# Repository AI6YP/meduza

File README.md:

## Meduza

Miniature control/logger board. Part of the Naut /nøyːt/ project.

### PCB v1

[Schematic (PDF)](eagle/meduza01/meduza01.pdf)

#### Features
 * Microchip microcontroller: [PIC24FJ64GA104](http://www.microchip.com/mymicrochip/filehandler.aspx?ddocname=en544252) / [DSPIC33EP128MC204](http://www.microchip.com/mymicrochip/filehandler.aspx?ddocname=en556386)
 * IRDA transceiver (2 Mibit/s) [TFDU6300](http://media.digikey.com/pdf/Data%20Sheets/Vishay%20Semiconductors/TFDU6300.pdf)
 * 3D Magnetometer [MAG3110L](http://cache.freescale.com/files/sensors/doc/data_sheet/MAG3110.pdf)
 * 3D Accelerometer [MMA8452QL](http://cache.freescale.com/files/sensors/doc/data_sheet/MMA8452Q.pdf)
 * 3D Giro [L3G4200D](http://www.st.com/web/en/resource/technical/document/datasheet/CD00265057.pdf)
 * temperature sensor [MCP9800](http://www.microchip.com/mymicrochip/filehandler.aspx?ddocname=en021183)
 * 1-cell LiPo battery PMIC [MCP73831T](http://www.microchip.com/mymicrochip/filehandler.aspx?ddocname=en025112)
 * microSD card socket (up-to 32GB)
 * analog/digital IO for externals sensors
 * Inductive charging circuitry (external)

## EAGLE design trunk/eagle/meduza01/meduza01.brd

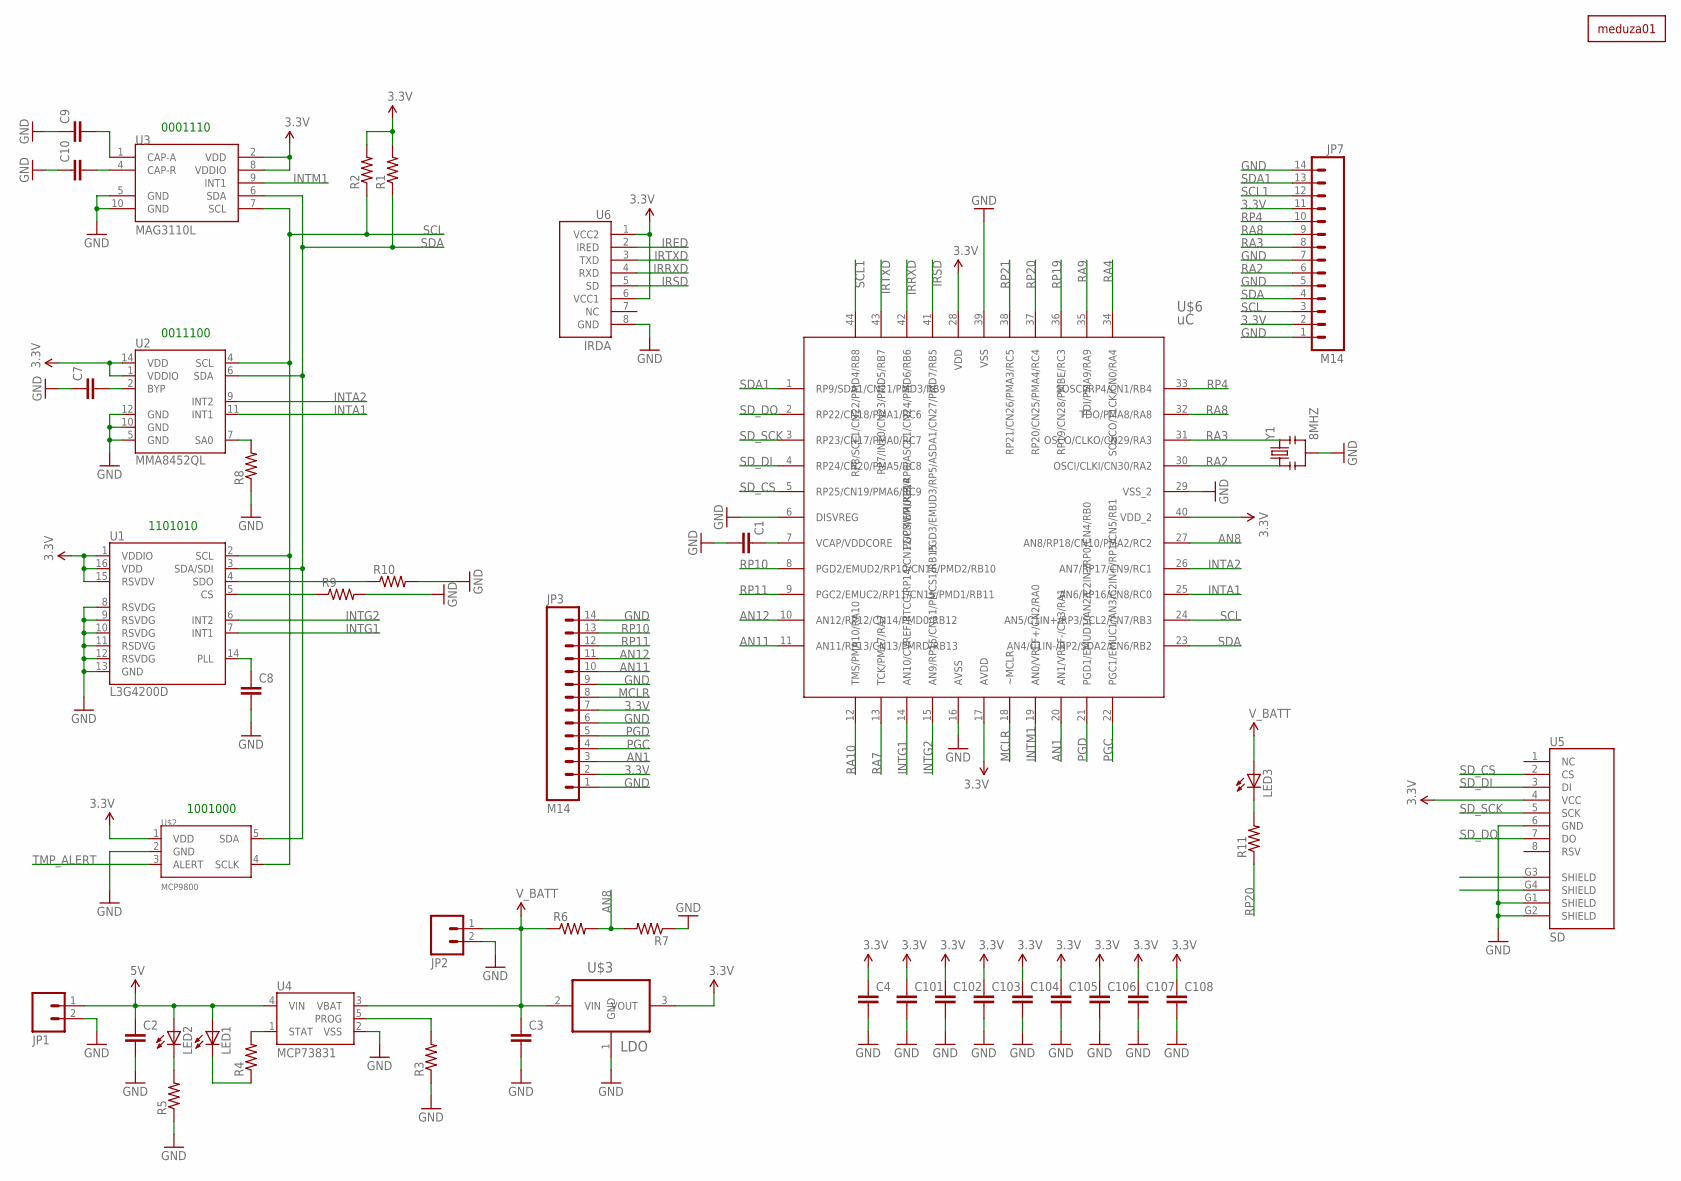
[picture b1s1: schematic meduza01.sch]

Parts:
C1, C7, C8, C9, C10, C101, C102, C103, C104, C105, C106, C107, C108: CAP0603-CAP; 0603-CAP
C2, C3, C4: CAP0805; 0805
JP1, JP2: M02PTH; 1X02
JP3, JP7: M14; 1X14
LED1, LED2, LED3: LED1206; LED-1206
R1, R2, R3, R4, R5, R6, R7, R8, R9, R10, R11: RESISTOR0603-RES; 0603-RES
U1: L3G4200D; LGA16-4X4
U2: MMA8452QL; QFN-16_0.5MM-EXTRA
U3: MAG3110L; DFN-10-EXTRA
U4: MCP73831; SOT23-5
U5: SD; MOLEX-SD-47309
U6: IRDA; TFDU6300
U$1: MEDUZA01
U$2: MCP9800; SOT23-5
U$3: LDO; SOT89R
U$6: uC; QFP80P1200X1200X120-44N
Y1: 8MHZ; RESONATOR-SMD

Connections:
3.3V: C4.1, C101.1, C102.1, C103.1, C104.1, C105.1, C106.1, C107.1, C108.1, JP3.2, JP3.7, JP7.2, JP7.11, R1.2, R2.2, U1.1 (VDDIO), U1.15 (RSVDV), U1.16 (VDD), U2.1 (VDDIO), U2.14 (VDD), U3.2 (VDD), U3.8 (VDDIO), U5.4 (VCC), U6.1 (VCC2), U6.6 (VCC1), U$2.1 (VDD), U$3.3 (VOUT), U$6.17 (AVDD), U$6.28 (VDD), U$6.40 (VDD_2)
5V: C2.1, JP1.1, LED1.A, LED2.A, U4.4 (VIN)
ABYP: C7.2, U2.2 (BYP)
AN1: JP3.3, U$6.20 (AN1/VREF-/CN3/RA1)
AN8: R6.2, R7.2, U$6.27 (AN8/RP18/CN10/PMA2/RC2)
AN11: JP3.10, U$6.11 (AN11/RP13/CN13/PMRD/RB13)
AN12: JP3.11, U$6.10 (AN12/RP12/CN14/PMD0/RB12)
GCS: R9.1, U1.5 (CS)
GND: C1.2, C2.2, C3.2, C4.2, C7.1, C8.2, C9.1, C10.1, C101.2, C102.2, C103.2, C104.2, C105.2, C106.2, C107.2, C108.2, JP1.2, JP2.2, JP3.1, JP3.6, JP3.9, JP3.14, JP7.1, JP7.5, JP7.7, JP7.14, R3.1, R5.1, R7.1, R8.1, R9.2, R10.2, U1.8 (RSVDG), U1.9 (RSVDG), U1.10 (RSVDG), U1.11 (RSDVG), U1.12 (RSVDG), U1.13 (GND), U2.5 (GND), U2.10 (GND), U2.12 (GND), U3.5 (GND), U3.10 (GND), U4.2 (VSS), U5.6 (GND), U5.G1 (SHIELD), U5.G2 (SHIELD), U6.8 (GND), U$2.2 (GND), U$3.1 (GND), U$6.6 (DISVREG), U$6.16 (AVSS), U$6.29 (VSS_2), U$6.39 (VSS), Y1.2
GPLL: C8.1, U1.14 (PLL)
GSDO: R10.1, U1.4 (SDO)
INTA1: U2.11 (INT1), U$6.25 (AN6/RP16/CN8/RC0)
INTA2: U2.9 (INT2), U$6.26 (AN7/RP17/CN9/RC1)
INTG1: U1.7 (INT1), U$6.14 (AN10/CVREF/RTCC/RP14/CN12/PMWR/RB14)
INTG2: U1.6 (INT2), U$6.15 (AN9/RP15/CN11/PMCS1/RB15)
INTM1: U3.9 (INT1), U$6.19 (AN0/VREF+/CN2/RA0)
IRED: U6.2 (IRED)
IRRXD: U6.4 (RXD), U$6.42 (PGC3/EMUC3/RP6/ASCL1/CN24/PMD6/RB6)
IRSD: U6.5 (SD), U$6.41 (PGD3/EMUD3/RP5/ASDA1/CN27/PMD7/RB5)
IRTXD: U6.3 (TXD), U$6.43 (RP7/INT0/CN23/PMD5/RB7)
MCAPA: C9.2, U3.1 (CAP-A)
MCAPR: C10.2, U3.4 (CAP-R)
MCLR: JP3.8, U$6.18 (~MCLR)
unnamed: C1.1, U$6.7 (VCAP/VDDCORE)
unnamed: LED3.C, R11.2
unnamed: LED1.C, R4.1
unnamed: LED2.C, R5.2
PGC: JP3.4, U$6.22 (PGC1/EMUC1/AN3/C2IN+/RP1/CN5/RB1)
PGD: JP3.5, U$6.21 (PGD1/EMUD1/AN2/C2IN-/RP0/CN4/RB0)
PROG: R3.2, U4.5 (PROG)
RA2: JP7.6, U$6.30 (OSCI/CLKI/CN30/RA2), Y1.1
RA3: JP7.8, U$6.31 (OSCO/CLKO/CN29/RA3), Y1.3
RA4: U$6.34 (SOSCO/T1CK/CN0/RA4)
RA7: U$6.13 (TCK/PMA7/RA7)
RA8: JP7.9, U$6.32 (TDO/PMA8/RA8)
RA9: U$6.35 (TDI/PMA9/RA9)
RA10: U$6.12 (TMS/PMA10/RA10)
RP4: JP7.10, U$6.33 (SOSCI/RP4/CN1/RB4)
RP10: JP3.13, U$6.8 (PGD2/EMUD2/RP10/CN16/PMD2/RB10)
RP11: JP3.12, U$6.9 (PGC2/EMUC2/RP11/CN15/PMD1/RB11)
RP19: U$6.36 (RP19/CN28/PMBE/RC3)
RP20: R11.1, U$6.37 (RP20/CN25/PMA4/RC4)
RP21: U$6.38 (RP21/CN26/PMA3/RC5)
SA0: R8.2, U2.7 (SA0)
SCL: JP7.3, R2.1, U1.2 (SCL), U2.4 (SCL), U3.7 (SCL), U$2.4 (SCLK), U$6.24 (AN5/C1IN+/RP3/SCL2/CN7/RB3)
SCL1: JP7.12, U$6.44 (RP8/SCL1/CN22/PMD4/RB8)
SDA: JP7.4, R1.1, U1.3 (SDA/SDI), U2.6 (SDA), U3.6 (SDA), U$2.5 (SDA), U$6.23 (AN4/C1IN-/RP2/SDA2/CN6/RB2)
SDA1: JP7.13, U$6.1 (RP9/SDA1/CN21/PMD3/RB9)
SD_CS: U5.2 (CS), U$6.5 (RP25/CN19/PMA6/RC9)
SD_DI: U5.3 (DI), U$6.4 (RP24/CN20/PMA5/RC8)
SD_DO: U5.7 (DO), U$6.2 (RP22/CN18/PMA1/RC6)
SD_SCK: U5.5 (SCK), U$6.3 (RP23/CN17/PMA0/RC7)
STAT: R4.2, U4.1 (STAT)
TMP_ALERT: U$2.3 (ALERT)
V_BATT: C3.1, JP2.1, LED3.A, R6.1, U4.3 (VBAT), U$3.2 (VIN)

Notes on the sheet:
1001000
1101010
0011100
0001110

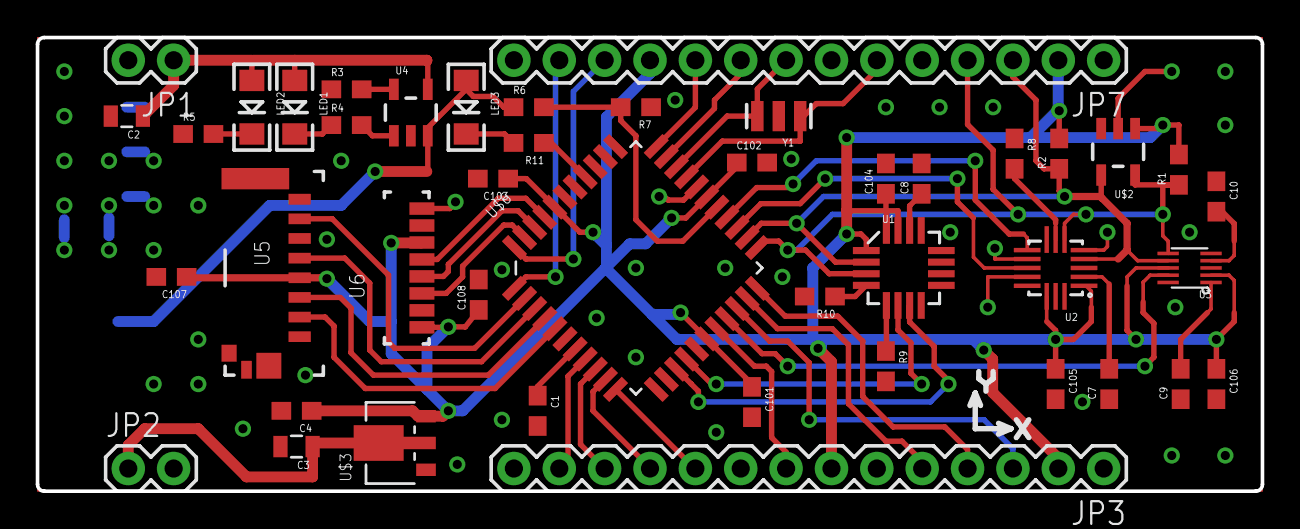
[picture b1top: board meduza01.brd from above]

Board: 2 copper layers, 68.6 x 25.4 mm, 45 parts (1 on the bottom side), 47 nets.

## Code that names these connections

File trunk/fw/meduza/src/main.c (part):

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	AD1PCFGbits.PCFG1 = 1;

	// ******************************************************** RP Inputs
	// RPINR0  [12:8] = INT1   = 16 (RP16) INTA1 <-- RC0
	RPINR0  = 0x1000;
	// RPINR18 [12:8] = U1CTSR = 31 (unselected)
	// RPINR18  [4:0] = U1RXR  = 6  (RP6)  IRRXD <-- RB6
	RPINR18 = 0x1F06;
	// RPINR7  [12:8] = IC2    = 31 (Stub)
	// RPINR7   [4:0] = IC1    = 6  (RP6)  IRRXD <-- RB6
	RPINR7  = 0x1F06;
	// RPINR7  [12:8] = SCK1   = 31 (Stub)
	// RPINR7   [4:0] = SDI1   = 22 (RP22) SD_DO <-- RC6  MISO
	RPINR20 = 0x1F16;

	// ******************************************************** RP Outputs
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
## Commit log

2012-12-11 repo restart
2012-12-13 Created wiki page through web user interface.
2012-12-13 Edited wiki page Resources through web user interface.
2012-12-17 meduza01 board files
2013-01-06 Meduza PCB photo from BatchPCB foundry
2013-01-06 mime type fix
2013-01-06 small version of photo
2013-01-17 I2C support added
2013-01-19 new PCB photos
2013-01-23 updated SD card, IRDA interfaces for Meduza01 board
2013-01-26 moved constants into config.h
2013-01-26 Morse signaling implementation
2013-01-26 IRDA mode in cleanex
2013-01-26 meduza project files
2013-01-26 added empty log folder
2013-01-26 some update
2013-01-26 ploting code
2013-01-28 minor fixes
2013-01-29 better SD write
2013-02-05 first sign of working ACC!
2013-02-13 octave script updated
2013-02-13 first working version with ACC only.
2013-02-14 OEL style fix
2013-02-14 minor play around I2C
2013-04-28 Edited wiki page MCU through web user interface.
2015-03-15 added schematic pdf
2015-03-21 board status images added
2015-03-21 board status text added

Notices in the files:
parts and their libraries:
SparkFun: Licensing: CC v3.0 Share-Alike You are welcome to use this library for commercial purposes.
